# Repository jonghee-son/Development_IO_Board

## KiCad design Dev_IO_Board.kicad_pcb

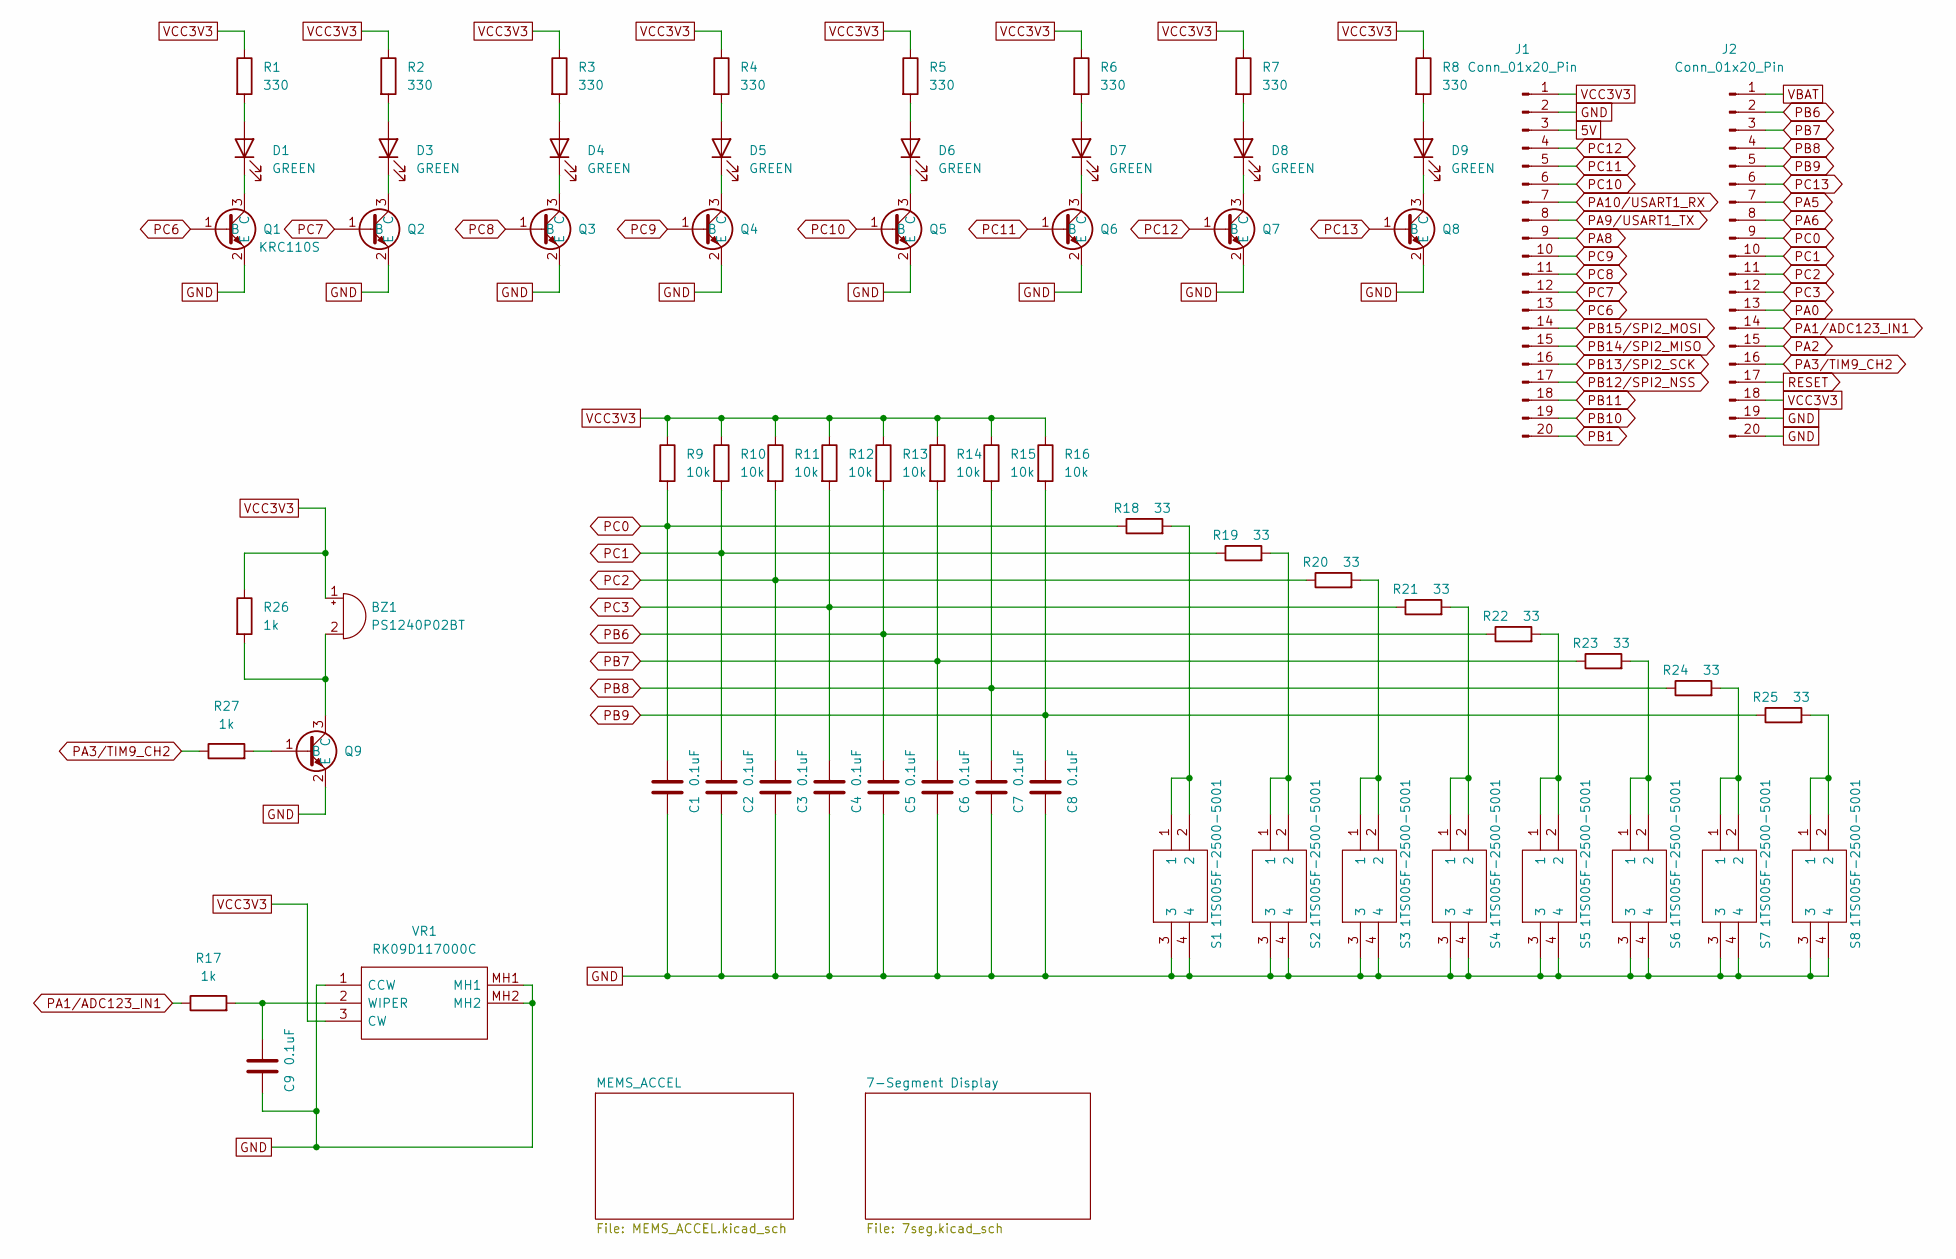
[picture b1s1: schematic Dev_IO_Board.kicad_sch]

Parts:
BZ1: PS1240P02BT; Buzzer_TDK_PS1240P02BT_D12.2mm_H6.5mm
C1, C2, C3, C4, C5, C6, C7, C8, C9: 0.1uF; C_0603_1608Metric_Pad1.08x0.95mm_HandSolder
D1, D3, D4, D5, D6, D7, D8, D9: GREEN; LED_0603_1608Metric_Pad1.05x0.95mm_HandSolder
J1, J2: Conn_01x20_Pin; PinSocket_1x20_P2.54mm_Vertical
Q1: KRC110S; SOT-23
Q2, Q3, Q4, Q5, Q6, Q7, Q8, Q9: SOT-23
R1, R2, R3, R4, R5, R6, R7, R8: 330; R_0603_1608Metric_Pad0.98x0.95mm_HandSolder
R9, R10, R11, R12, R13, R14, R15, R16: 10k; R_0603_1608Metric_Pad0.98x0.95mm_HandSolder
R17, R26, R27: 1k; R_0603_1608Metric_Pad0.98x0.95mm_HandSolder
R18, R19, R20, R21, R22, R23, R24, R25: 33; R_0603_1608Metric_Pad0.98x0.95mm_HandSolder
S1, S2, S3, S4, S5, S6, S7, S8: 1TS005F-2500-5001; 1TS005F25005001; Manufacturer_Part_Number 1TS005F-2500-5001
VR1: RK09D117000C; Manufacturer_Part_Number RK09D117000C; Mouser Part Number 688-RK09D117000C

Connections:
5V: J1.3
unnamed: BZ1.2 (+), Q9.3 (C), R26.2
unnamed: D1.2 (A), R1.2
unnamed: D1.1 (K), Q1.3 (C)
unnamed: D3.2 (A), R2.2
unnamed: D3.1 (K), Q2.3 (C)
unnamed: D4.2 (A), R3.2
unnamed: D4.1 (K), Q3.3 (C)
unnamed: D5.2 (A), R4.2
unnamed: D5.1 (K), Q4.3 (C)
unnamed: D6.2 (A), R5.2
unnamed: D6.1 (K), Q5.3 (C)
unnamed: D7.2 (A), R6.2
unnamed: D7.1 (K), Q6.3 (C)
unnamed: D8.2 (A), R7.2
unnamed: D8.1 (K), Q7.3 (C)
unnamed: D9.1 (K), Q8.3 (C)
unnamed: Q9.1 (B), R27.2
unnamed: R18.2, S1.1, S1.2
unnamed: R19.2, S2.1, S2.2
unnamed: R20.2, S3.1, S3.2
unnamed: R21.2, S4.1, S4.2
unnamed: R22.2, S5.1, S5.2
unnamed: R23.2, S6.1, S6.2
unnamed: R24.2, S7.1, S7.2
unnamed: R25.2, S8.1, S8.2
unnamed: C9.1, R17.2, VR1.2 (WIPER)
PA0: J2.13; also elsewhere on the board
PA1/ADC123_IN1: J2.14, R17.1
PA2: J2.15; also elsewhere on the board
PA3/TIM9_CH2: J2.16, R27.1
PA5: J2.7; also elsewhere on the board
PA6: J2.8; also elsewhere on the board
PA8: J1.9; also elsewhere on the board
PA9/USART1_TX: J1.8
PA10/USART1_RX: J1.7
PB1: J1.20; also elsewhere on the board
PB6: C5.1, J2.2, R13.2, R22.1
PB7: C6.1, J2.3, R14.2, R23.1
PB8: C7.1, J2.4, R15.2, R24.1
PB9: C8.1, J2.5, R16.2, R25.1
PB10: J1.19; also elsewhere on the board
PB11: J1.18; also elsewhere on the board
PB12/SPI2_NSS: J1.17; also elsewhere on the board
PB13/SPI2_SCK: J1.16; also elsewhere on the board
PB14/SPI2_MISO: J1.15; also elsewhere on the board
PB15/SPI2_MOSI: J1.14; also elsewhere on the board
PC0: C1.1, J2.9, R9.2, R18.1
PC1: C2.1, J2.10, R10.2, R19.1
PC2: C3.1, J2.11, R11.2, R20.1
PC3: C4.1, J2.12, R12.2, R21.1
PC6: J1.13, Q1.1 (B)
PC7: J1.12, Q2.1 (B)
PC8: J1.11, Q3.1 (B)
PC9: J1.10, Q4.1 (B)
PC10: J1.6, Q5.1 (B)
PC11: J1.5, Q6.1 (B)
PC12: J1.4, Q7.1 (B)
PC13: J2.6, Q8.1 (B)
RESET: J2.17
VBAT: J2.1

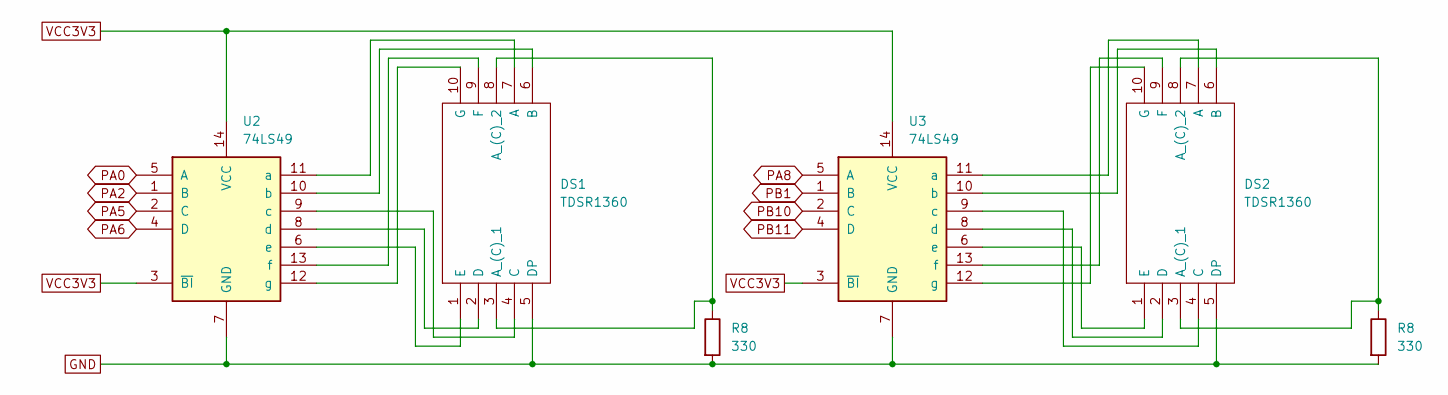
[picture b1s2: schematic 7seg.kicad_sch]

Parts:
DS1, DS2: TDSR1360; DIPS1524W55P254L1225H710Q10N; Manufacturer_Part_Number TDSR1360; Mouser Part Number 78-TDSR1360
R8: 330; R_0603_1608Metric_Pad0.98x0.95mm_HandSolder
U2, U3: 74LS49; DIP-14_W7.62mm_Socket

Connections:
unnamed: DS1.7 (A), U2.11 (a)
unnamed: DS1.6 (B), U2.10 (b)
unnamed: DS1.4 (C), U2.9 (c)
unnamed: DS1.2 (D), U2.8 (d)
unnamed: DS1.1 (E), U2.6 (e)
unnamed: DS1.9 (F), U2.13 (f)
unnamed: DS1.10 (G), U2.12 (g)
unnamed: DS2.7 (A), U3.11 (a)
unnamed: DS2.6 (B), U3.10 (b)
unnamed: DS2.4 (C), U3.9 (c)
unnamed: DS2.2 (D), U3.8 (d)
unnamed: DS2.1 (E), U3.6 (e)
unnamed: DS2.9 (F), U3.13 (f)
unnamed: DS2.10 (G), U3.12 (g)
PA0: U2.5 (A); also elsewhere on the board
PA2: U2.1 (B); also elsewhere on the board
PA5: U2.2 (C); also elsewhere on the board
PA6: U2.4 (D); also elsewhere on the board
PA8: U3.5 (A); also elsewhere on the board
PB1: U3.1 (B); also elsewhere on the board
PB10: U3.2 (C); also elsewhere on the board
PB11: U3.4 (D); also elsewhere on the board

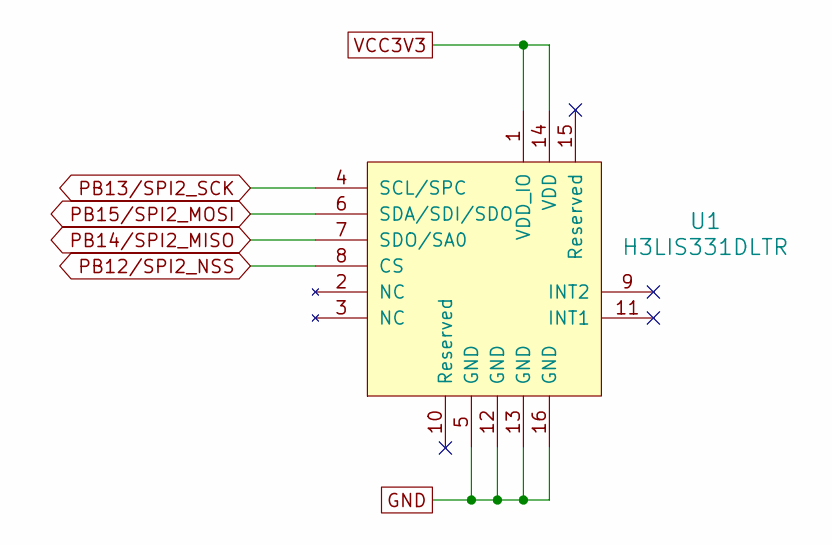
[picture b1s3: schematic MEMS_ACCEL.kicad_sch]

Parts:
U1: H3LIS331DLTR; TFLGA-16_3x3mm; MPN H3LIS331DLTR; Digi-Key_PN 497-13903-1-ND

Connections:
PB12/SPI2_NSS: U1.8 (CS); also elsewhere on the board
PB13/SPI2_SCK: U1.4 (SCL/SPC); also elsewhere on the board
PB14/SPI2_MISO: U1.7 (SDO/SA0); also elsewhere on the board
PB15/SPI2_MOSI: U1.6 (SDA/SDI/SDO); also elsewhere on the board

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
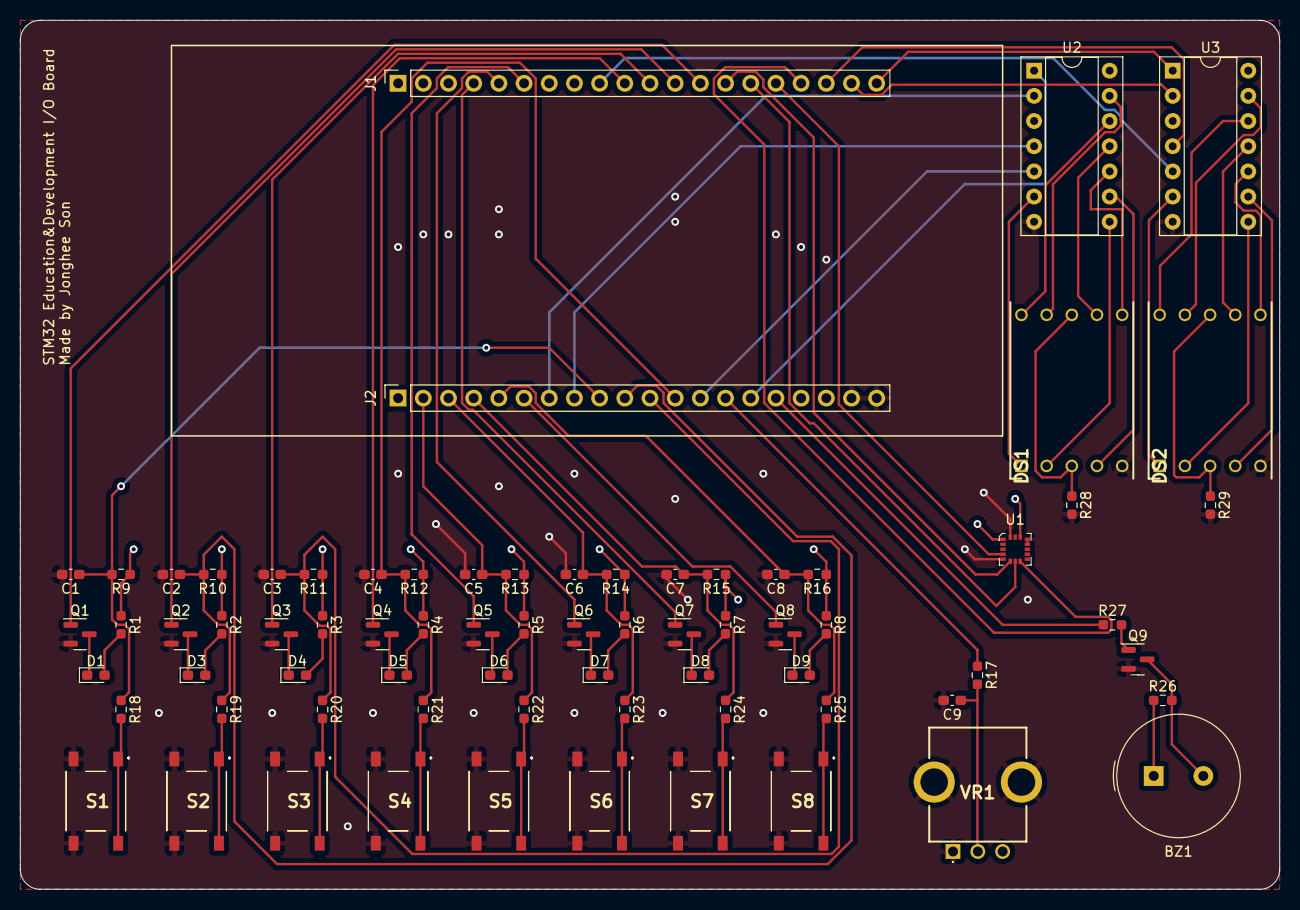
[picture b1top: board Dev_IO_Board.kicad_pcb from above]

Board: 4 copper layers, 127.0 x 87.6 mm, 72 parts (0 on the bottom side), 75 nets.

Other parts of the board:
R28, R29: 330; R_0603_1608Metric_Pad0.98x0.95mm_HandSolder

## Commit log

2023-12-22 Create LICENSE
2023-12-22 Added schematics
2023-12-25 Changed segment display to TDSR1360
2023-12-25 Updated schematics
